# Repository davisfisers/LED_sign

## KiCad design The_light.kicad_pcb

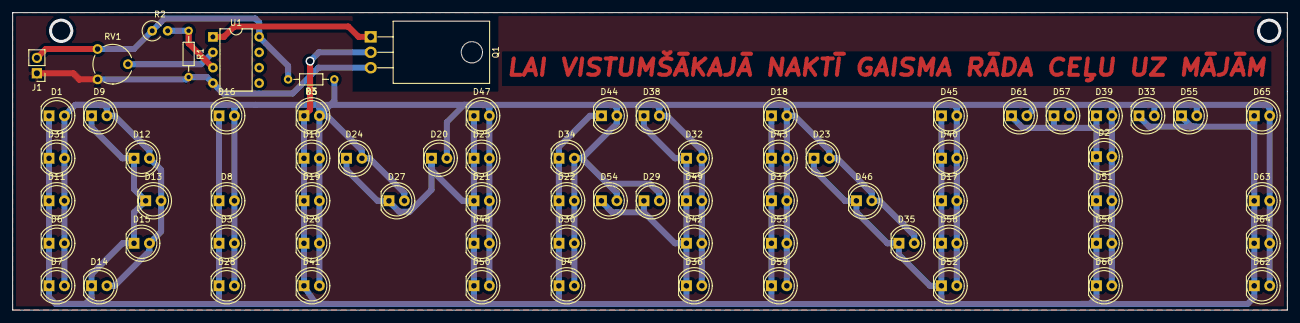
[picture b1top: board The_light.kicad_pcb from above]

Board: 2 copper layers, 210.0 x 49.0 mm, 72 parts (0 on the bottom side), 7 nets.

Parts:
D1, D2, D3, D4, D5, D6, D7, D8, D9, D10, D11, D12, D13, D14, D15, D16, D17, D18, D19, D20, D21, D22, D23, D24, D25, D26, D27, D28, D29, D30, D31, D32, D33, D34, D35, D36, D37, D38, D39, D40, D41, D42, D43, D44, D45, D46, D47, D48, D49, D50, D51, D52, D53, D54, D55, D56, D57, D58, D59, D60, D61, D62, D63, D64, D65: LED; LED_D5.0mm
J1: Conn_01x02; PinHeader_1x02_P2.54mm_Vertical
Q1: Q_NMOS_GDS; TO-220-3_Horizontal_TabDown
R1, R3: R; R_Axial_DIN0204_L3.6mm_D1.6mm_P7.62mm_Horizontal
R2: R_PHOTO; R_Axial_DIN0309_L9.0mm_D3.2mm_P2.54mm_Vertical
RV1: R_POT; Potentiometer_Piher_PT-6-V_Vertical
U1: Opamp_Dual_Generic; DIP-8_W7.62mm

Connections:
GND: J1.1, Q1.3, R1.2, RV1.1, U1.4
unnamed: D1.1, D2.1, D3.1, D4.1, D5.1, D6.1, D7.1, D8.1, D9.1, D10.1, D11.1, D12.1, D13.1, D14.1, D15.1, D16.1, D17.1, D18.1, D19.1, D20.1, D21.1, D22.1, D23.1, D24.1, D25.1, D26.1, D27.1, D28.1, D29.1, D30.1, D31.1, D32.1, D33.1, D34.1, D35.1, D36.1, D37.1, D38.1, D39.1, D40.1, D41.1, D42.1, D43.1, D44.1, D45.1, D46.1, D47.1, D48.1, D49.1, D50.1, D51.1, D52.1, D53.1, D54.1, D55.1, D56.1, D57.1, D58.1, D59.1, D60.1, D61.1, D62.1, D63.1, D64.1, D65.1, Q1.2
unnamed: D1.2, D2.2, D3.2, D4.2, D5.2, D6.2, D7.2, D8.2, D9.2, D10.2, D11.2, D12.2, D13.2, D14.2, D15.2, D16.2, D17.2, D18.2, D19.2, D20.2, D21.2, D22.2, D23.2, D24.2, D25.2, D26.2, D27.2, D28.2, D29.2, D30.2, D31.2, D32.2, D33.2, D34.2, D35.2, D36.2, D37.2, D38.2, D39.2, D40.2, D41.2, D42.2, D43.2, D44.2, D45.2, D46.2, D47.2, D48.2, D49.2, D50.2, D51.2, D52.2, D53.2, D54.2, D55.2, D56.2, D57.2, D58.2, D59.2, D60.2, D61.2, D62.2, D63.2, D64.2, D65.2, R3.1
unnamed: J1.2, R2.1, R3.2, RV1.3, U1.8
unnamed: Q1.1, U1.1
unnamed: R1.1, R2.2, U1.3
unnamed: RV1.2, U1.2

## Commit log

2019-03-23 upload
